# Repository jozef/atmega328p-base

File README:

NAME

    atmega328p-base - basic schematics and components for ATmega328p

DESCRIPTION

    Bootstrap KiCAD schematics for ATmega328p based projects. To rename set
    PROJECT_NAME env:

        export PROJECT_NAME=sixservo

    and clone/update/create new git/project repo:

        git clone https://github.com/jozef/atmega328p-base
        mv atmega328p-base $PROJECT_NAME
        cd $PROJECT_NAME
        rm -rf .git LICENSE Makefile README*
        ls | perl -lanE '$f=$b=$_;$b=~s/atmega328p-base//; system("mv", $f, $ENV{PROJECT_NAME}.$b)'
        perl -lanE 's/atmega328p-base/$ENV{PROJECT_NAME}/;say $_' -i $PROJECT_NAME*
        git init
        git add .

SEE ALSO

    https://blog.kutej.net/2020/10/ATmega328p-base

LICENSE

    This is free software & hardware, licensed under the MIT License.

AUTHOR

        Jozef Kutej

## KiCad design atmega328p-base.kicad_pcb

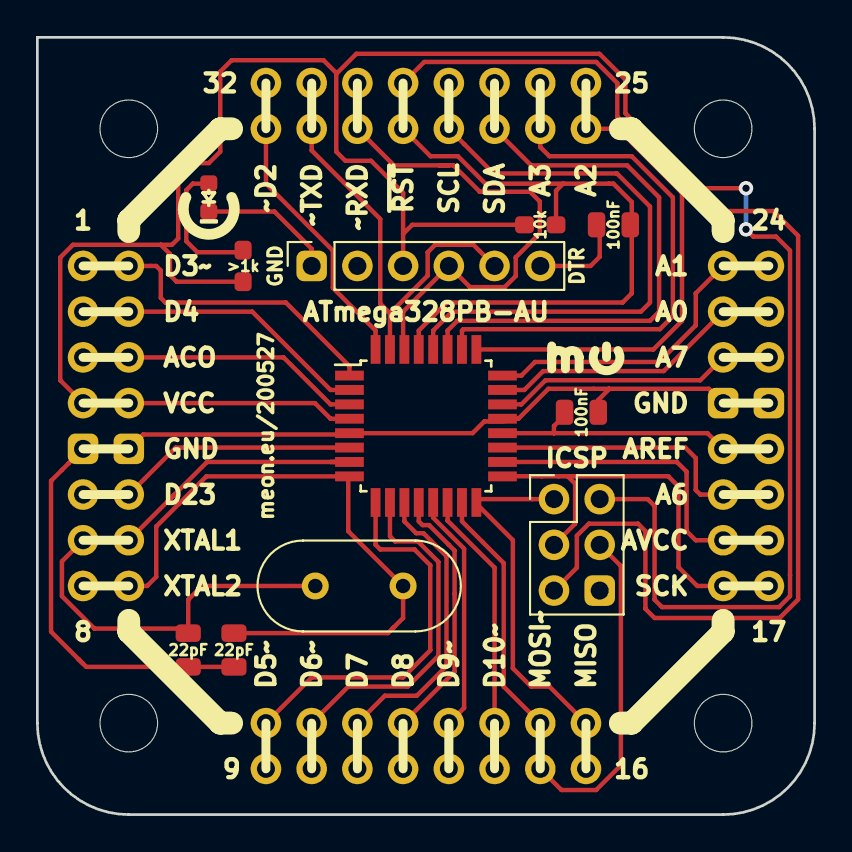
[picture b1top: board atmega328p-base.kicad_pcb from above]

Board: 2 copper layers, 43.2 x 43.2 mm, 19 parts (0 on the bottom side), 33 nets.

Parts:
C0, C2: 100nF; C_0805_2012Metric_no_lines
C11, C12: 22pF; C_0805_2012Metric_no_lines
D0: LED_Small; LED_0603_1608Metric_symbol
J0: ICSP; PinHeader_2x03_P2.54mm_Vertical
J1: USB_to_TTL; PinSocket_1x06_P2.54mm_Vertical
J31, J31#2: pins_1_8; PinHeader_1x08_P2.54mm_Vertical_no_lines
J32, J32#2: pins_8_16; PinHeader_1x08_P2.54mm_Vertical_no_lines
J33, J33#2: pins_17_24; PinHeader_1x08_P2.54mm_Vertical_no_lines
J34, J34#2: pins_25_32; PinHeader_1x08_P2.54mm_Vertical_no_lines
R0: 1k; C_0603_1608Metric_Pad1.05x0.95mm_HandSolder_no_lines
R1: 10k; C_0603_1608Metric_Pad1.05x0.95mm_HandSolder_no_lines
U1: ATmega328PB-AU; TQFP-32_7x7mm_P0.8mm
Y1: 16MHz; Crystal_HC49-U_Vertical

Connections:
A0: J33.7, J33#2.7, U1.23
A1: J33.8, J33#2.8, U1.24
A2: J34.1, J34#2.1, U1.25
A3: J34.2, J34#2.2, U1.26
A4_SDA: J34.3, J34#2.3, U1.27
A5_SCL: J34.4, J34#2.4, U1.28
A6: J33.3, J33#2.3, U1.19
A7: J33.6, J33#2.6, U1.22
ACO: J31.3, J31#2.3, U1.3
AREF: C0.1, J33.4, J33#2.4, U1.20
AVCC: J33.2, J33#2.2, U1.18
D2: J34.8, J34#2.8, U1.32
D3: J31.1, J31#2.1, U1.1
D4: J31.2, J31#2.2, U1.2
D5: J32.1, J32#2.1, U1.9
D6: J32.2, J32#2.2, U1.10
D7: J32.3, J32#2.3, U1.11
D8: J32.4, J32#2.4, U1.12
D9: J32.5, J32#2.5, U1.13
D10: J32.6, J32#2.6, U1.14
D11_MOSI: J0.4, J32.7, J32#2.7, U1.15
D12_MISO: J0.1, J32.8, J32#2.8, U1.16
D13_SCK: J0.3, J33.1, J33#2.1, U1.17
D23: J31.6, J31#2.6, U1.6
DTR: C2.2, J1.6
GND: C0.2, C11.1, C12.2, D0.1, J0.6, J1.1, J31.5, J31#2.5, J33.5, J33#2.5, U1.5, U1.21
unnamed: D0.2, R0.1
RXD: J1.4, J34.6, J34#2.6, U1.30
TXD: J1.5, J34.7, J34#2.7, U1.31
VCC: J0.2, J1.3, J31.4, J31#2.4, R0.2, R1.1, U1.4
XTAL1: C11.2, J31.7, J31#2.7, U1.7, Y1.2
XTAL2: C12.1, J31.8, J31#2.8, U1.8, Y1.1
~RST: C2.1, J0.5, J34.5, J34#2.5, R1.2, U1.29

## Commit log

2020-05-24 initial schematics
2020-05-24 label pins according to arduino ide
2020-05-27 add demo pcb
2020-05-28 bigger size C, tidy-up
